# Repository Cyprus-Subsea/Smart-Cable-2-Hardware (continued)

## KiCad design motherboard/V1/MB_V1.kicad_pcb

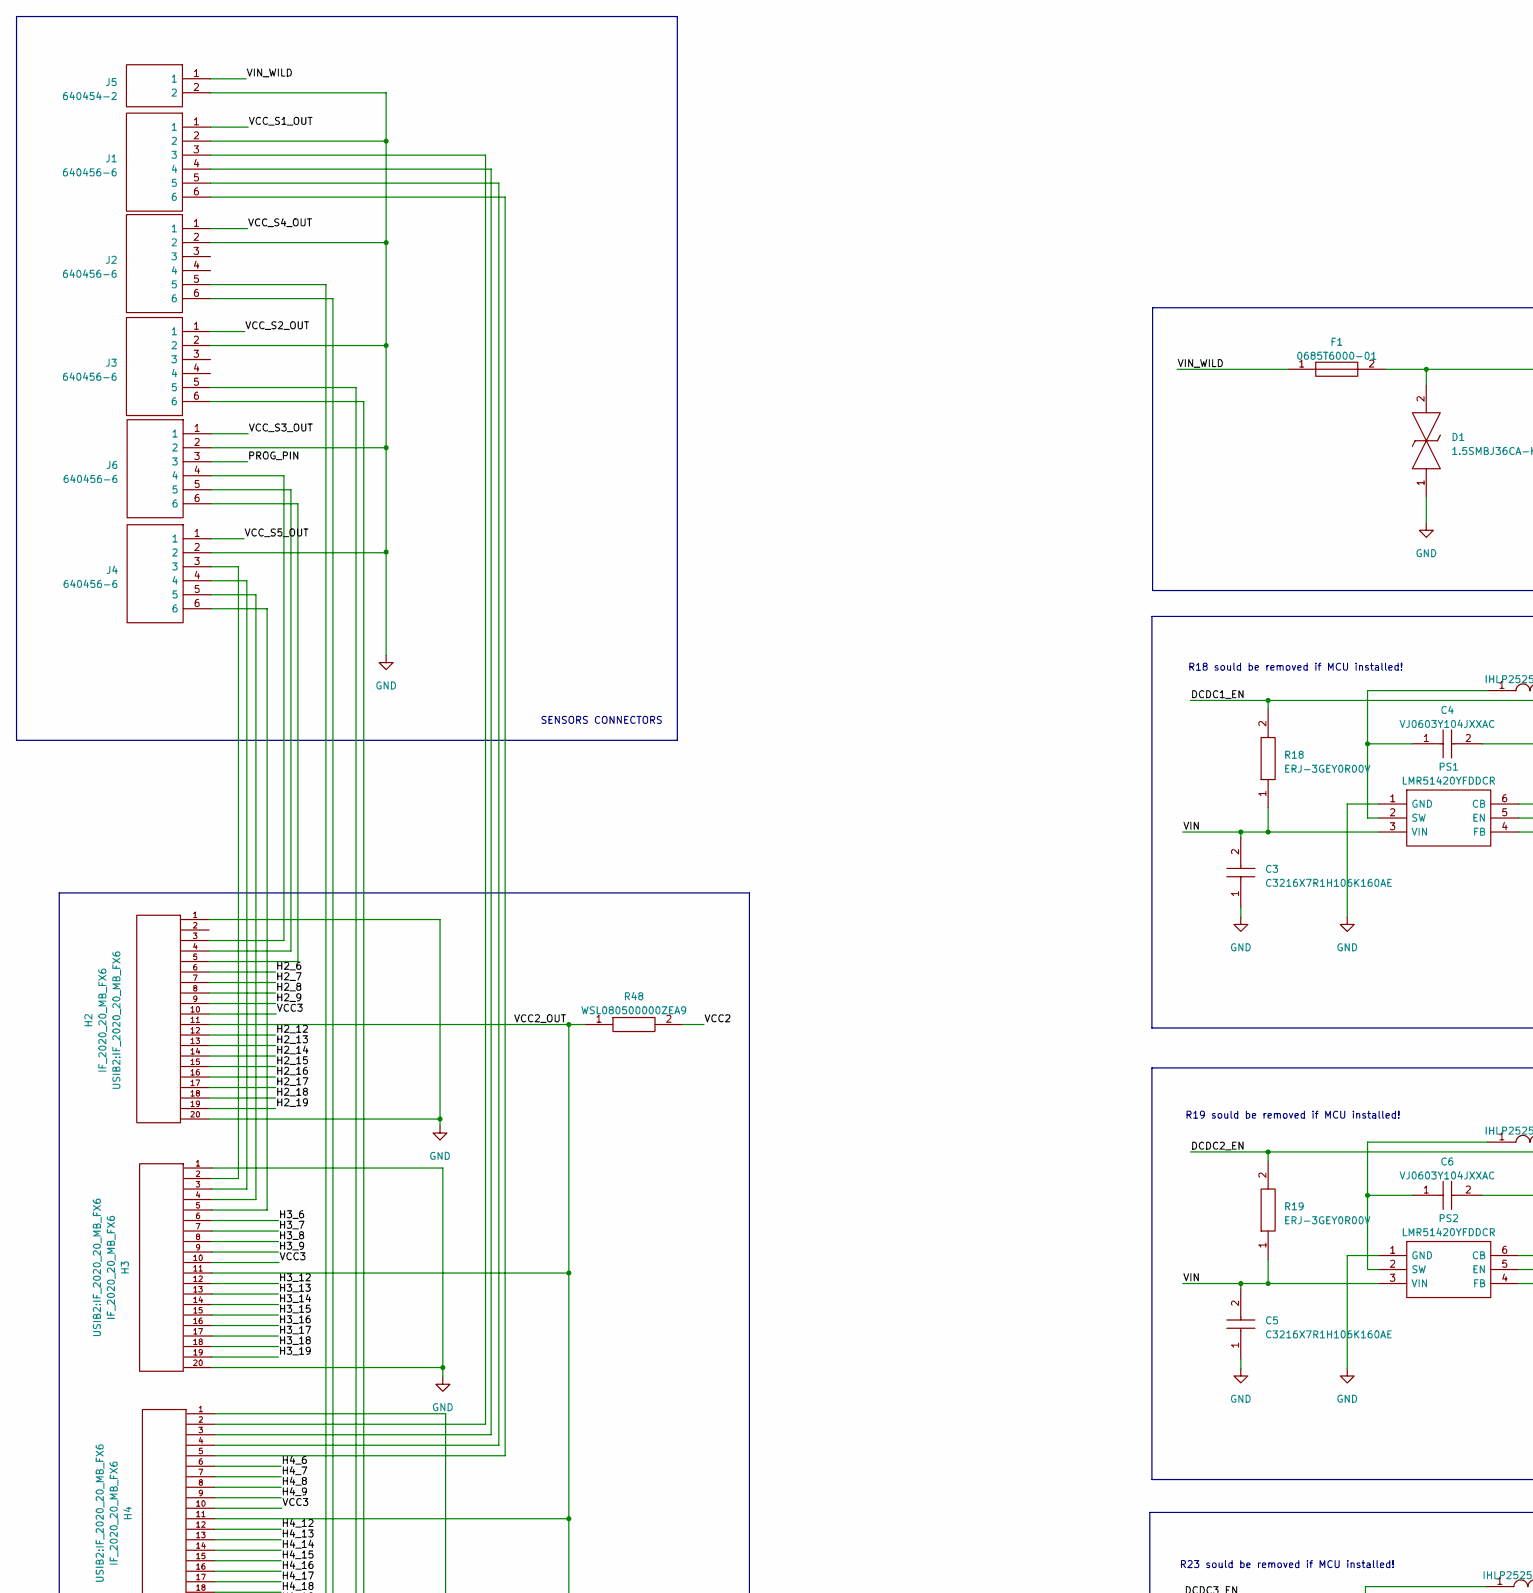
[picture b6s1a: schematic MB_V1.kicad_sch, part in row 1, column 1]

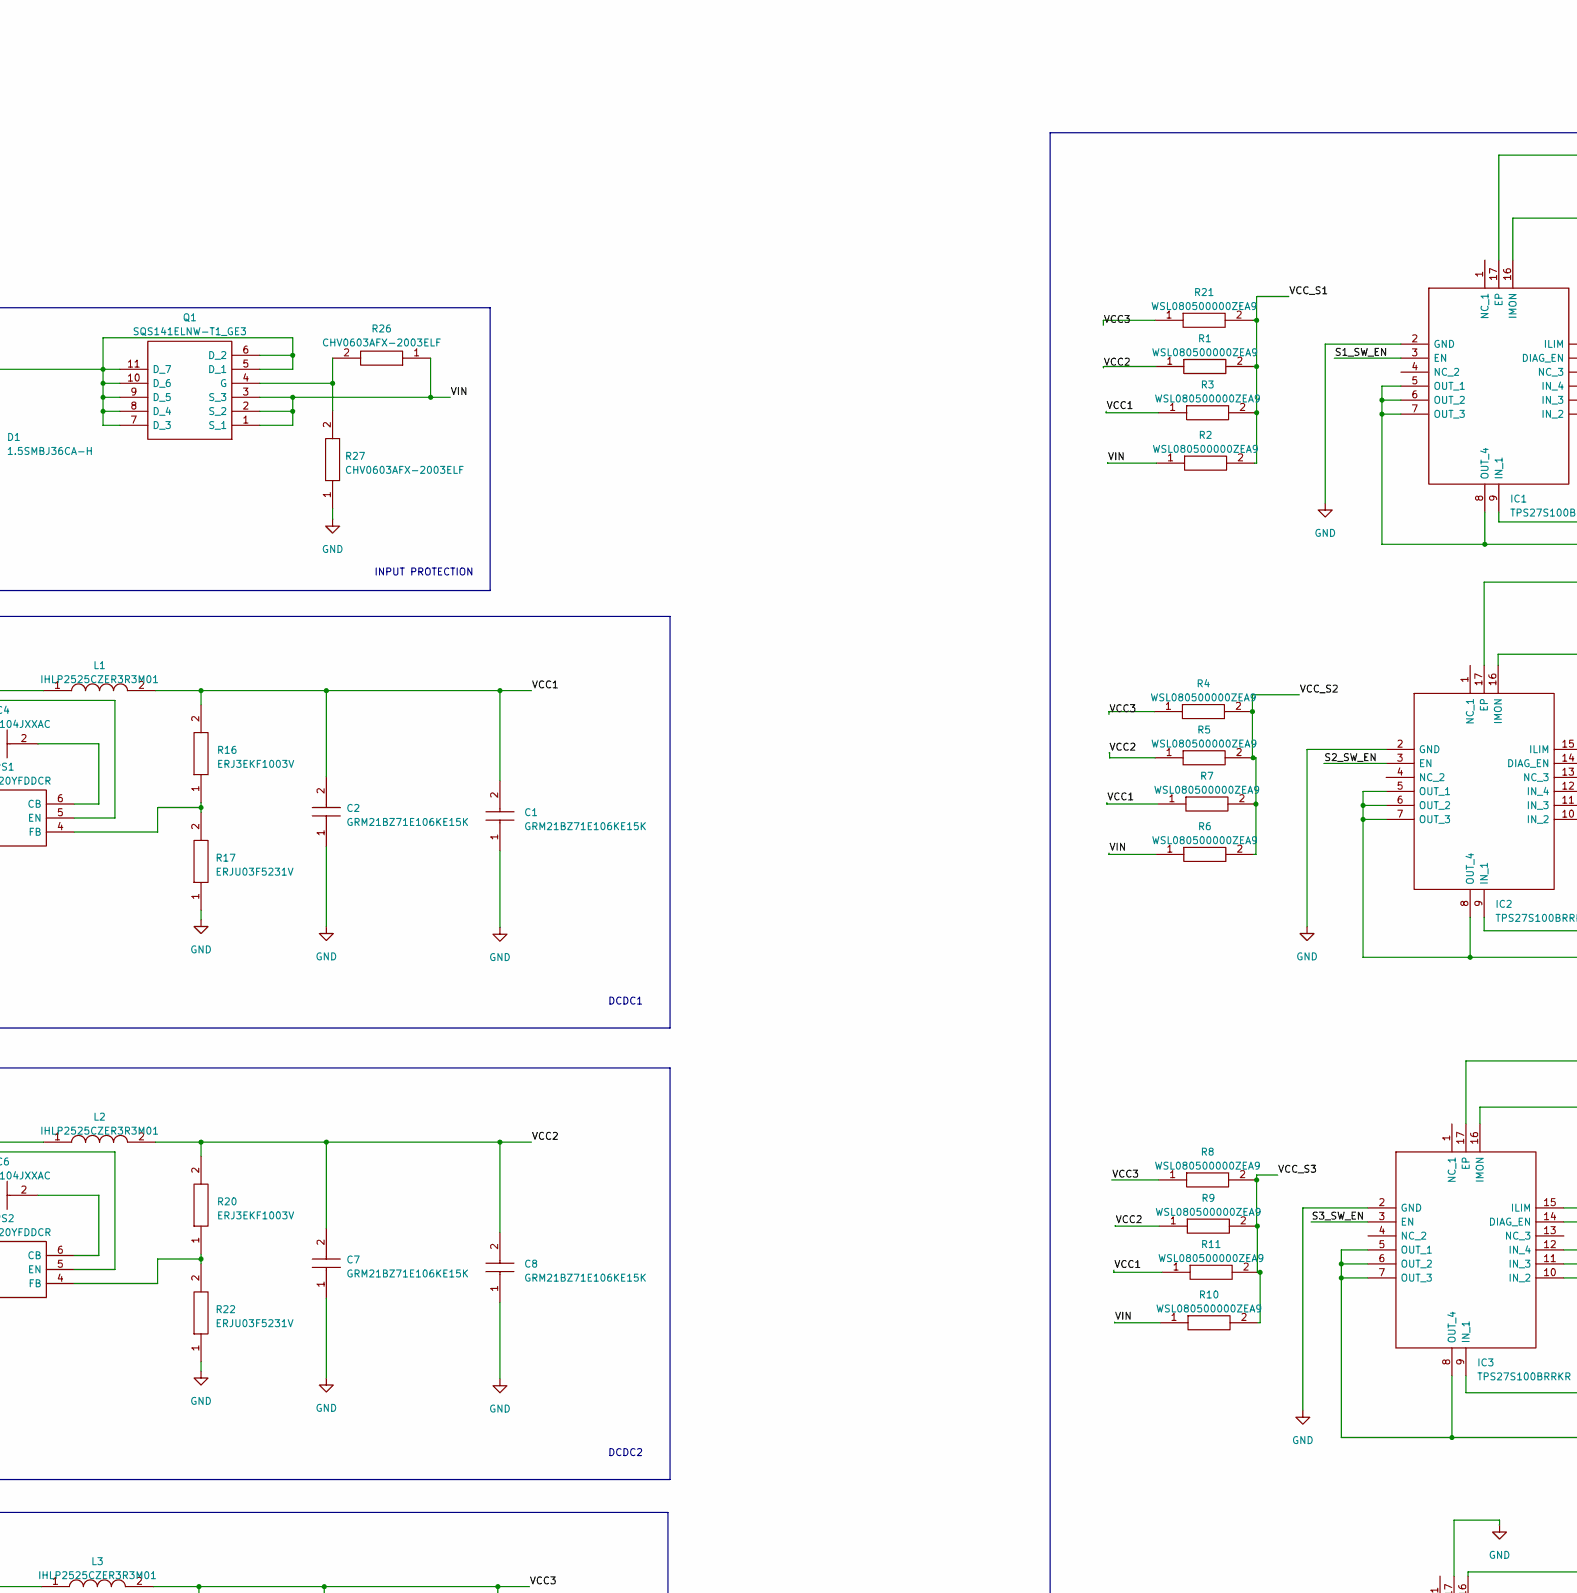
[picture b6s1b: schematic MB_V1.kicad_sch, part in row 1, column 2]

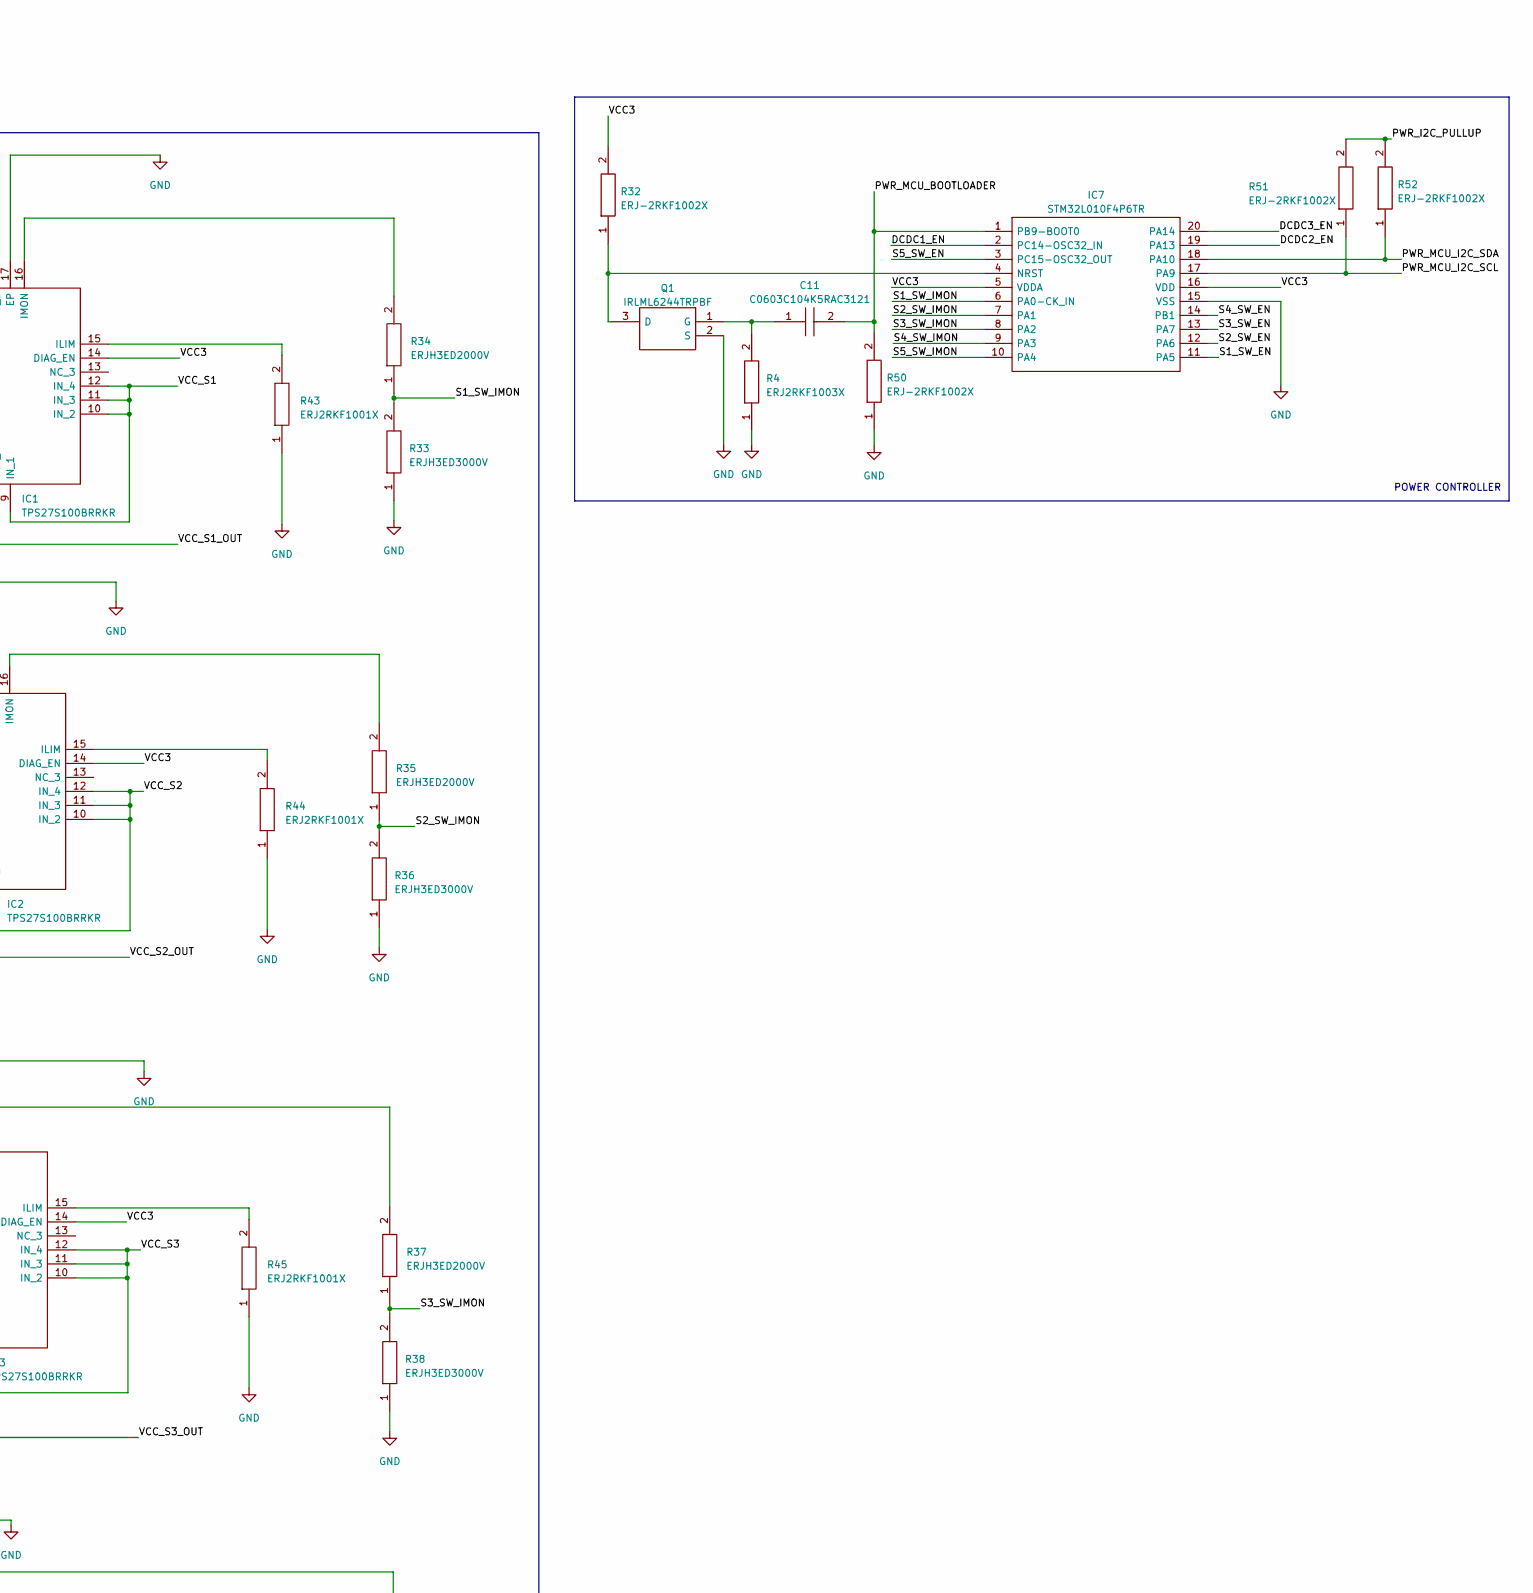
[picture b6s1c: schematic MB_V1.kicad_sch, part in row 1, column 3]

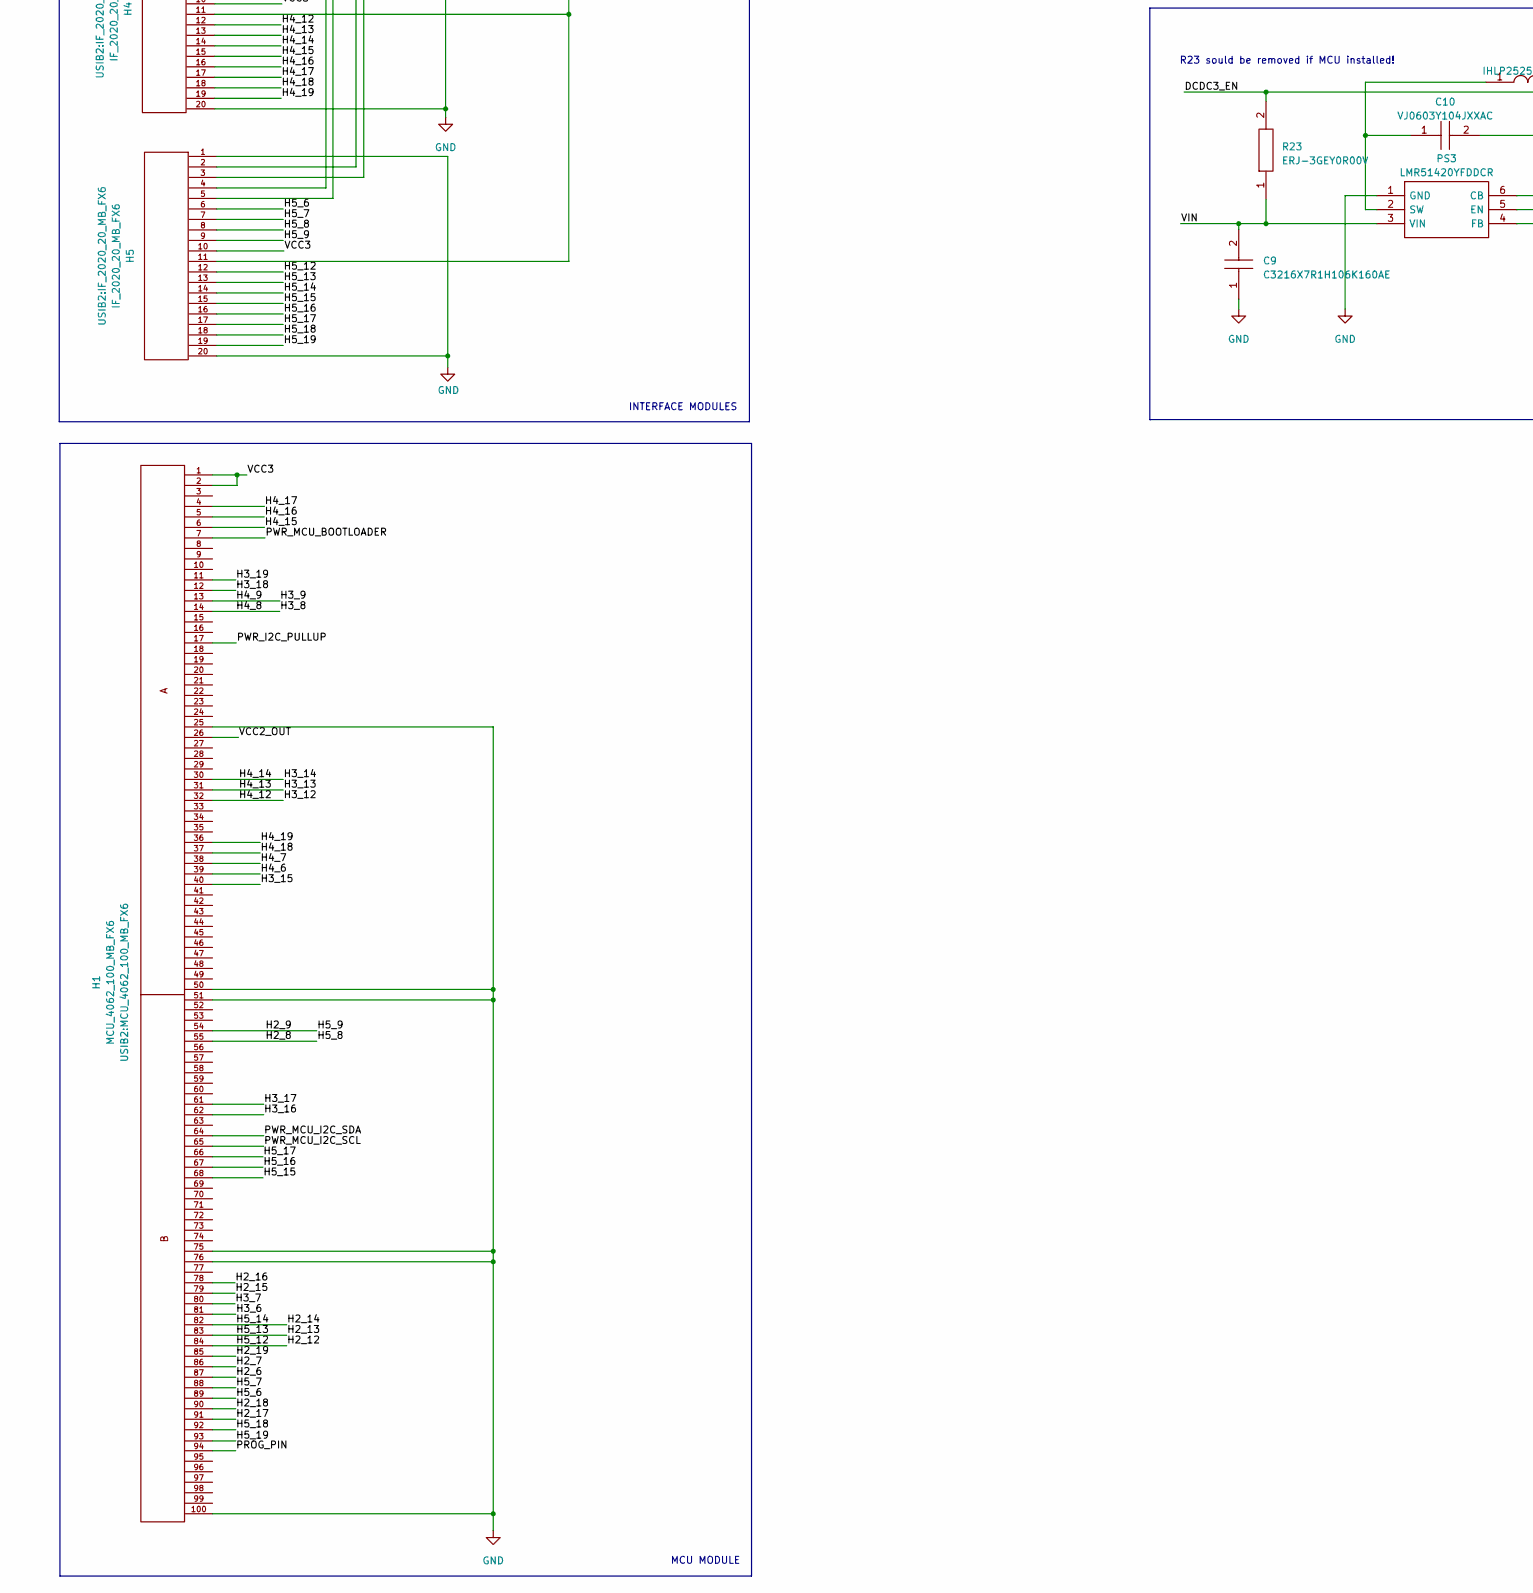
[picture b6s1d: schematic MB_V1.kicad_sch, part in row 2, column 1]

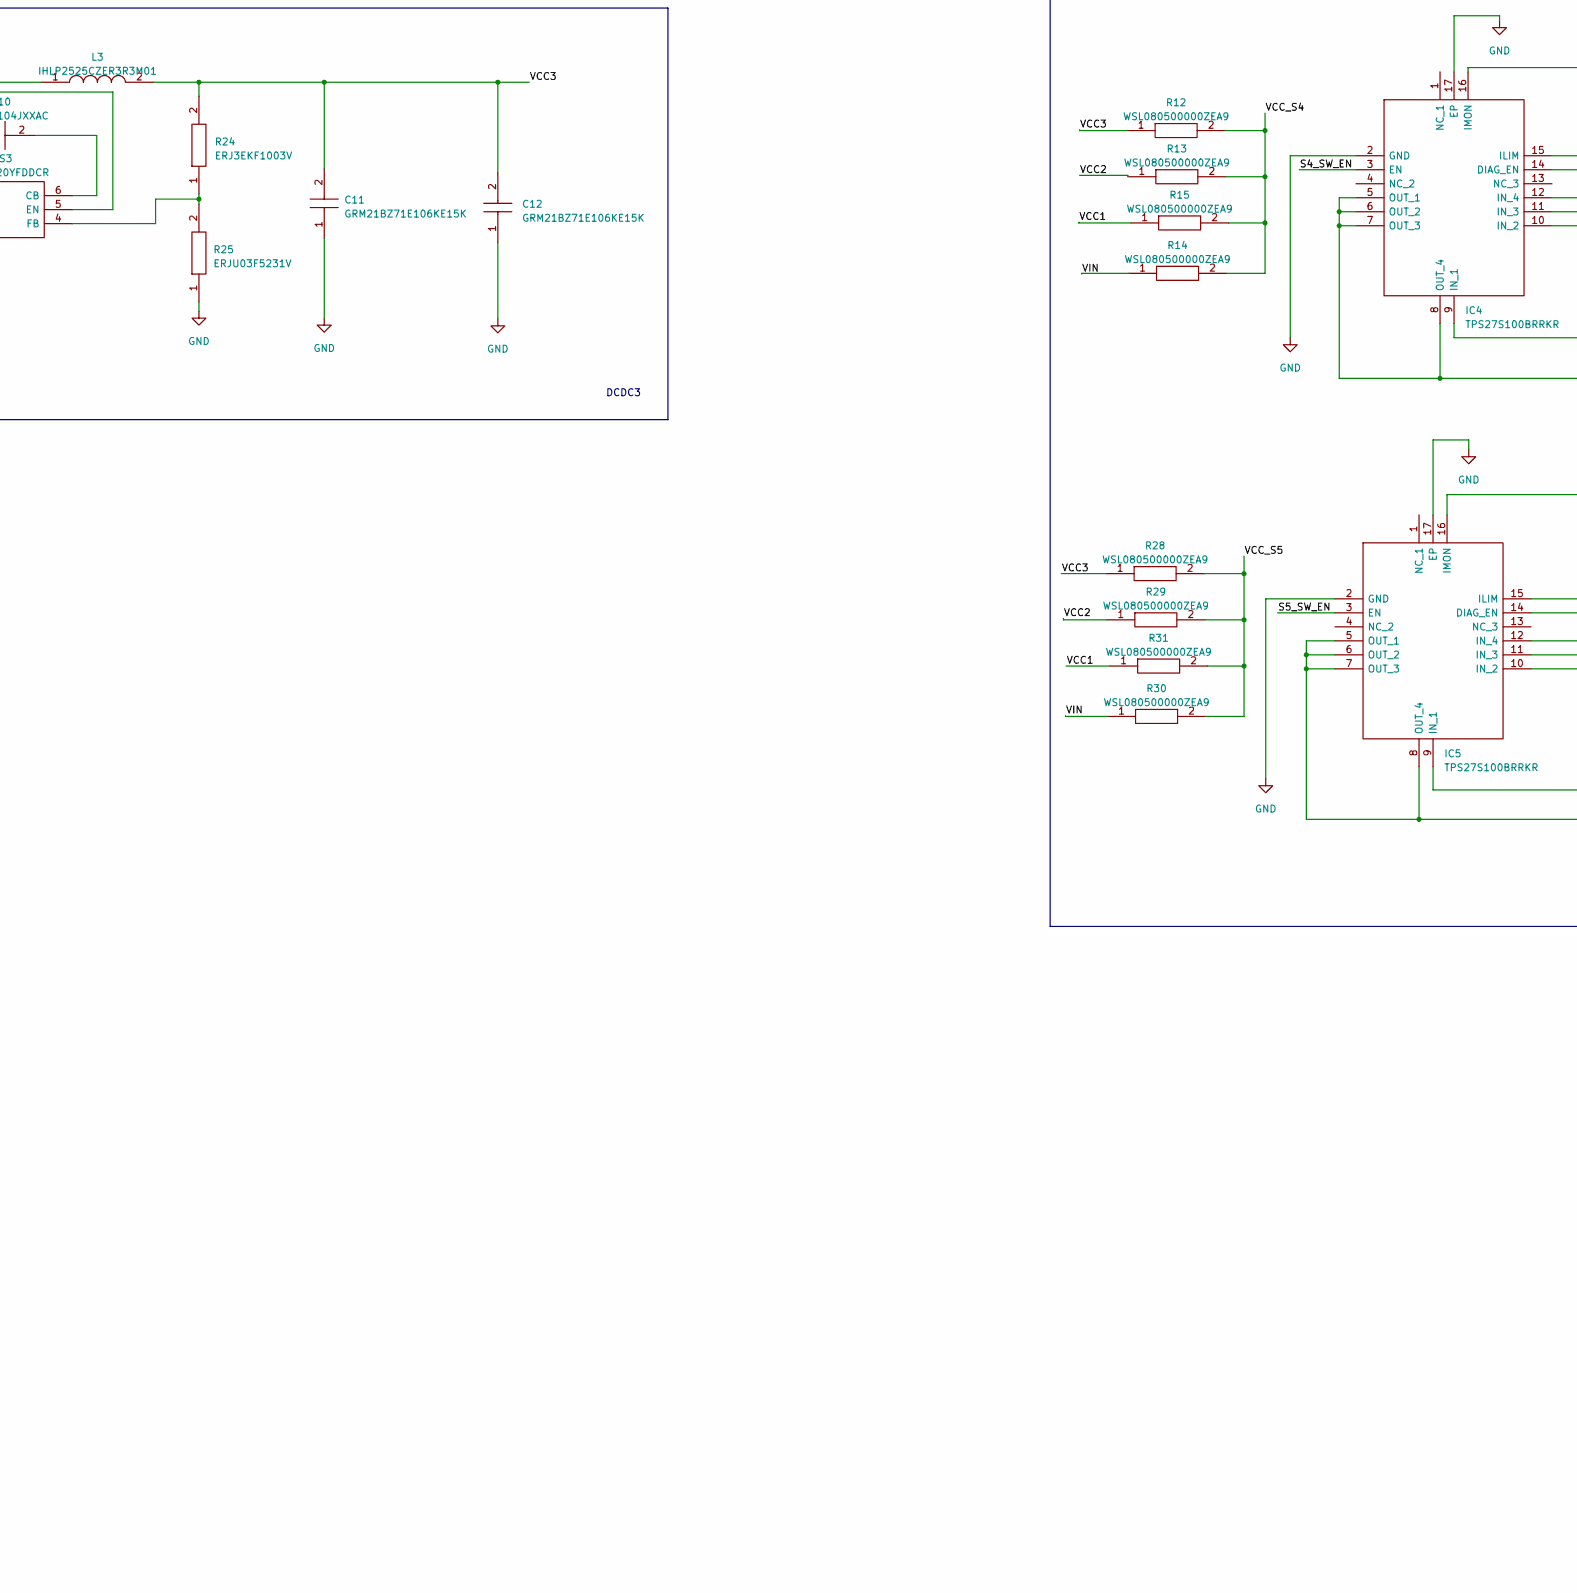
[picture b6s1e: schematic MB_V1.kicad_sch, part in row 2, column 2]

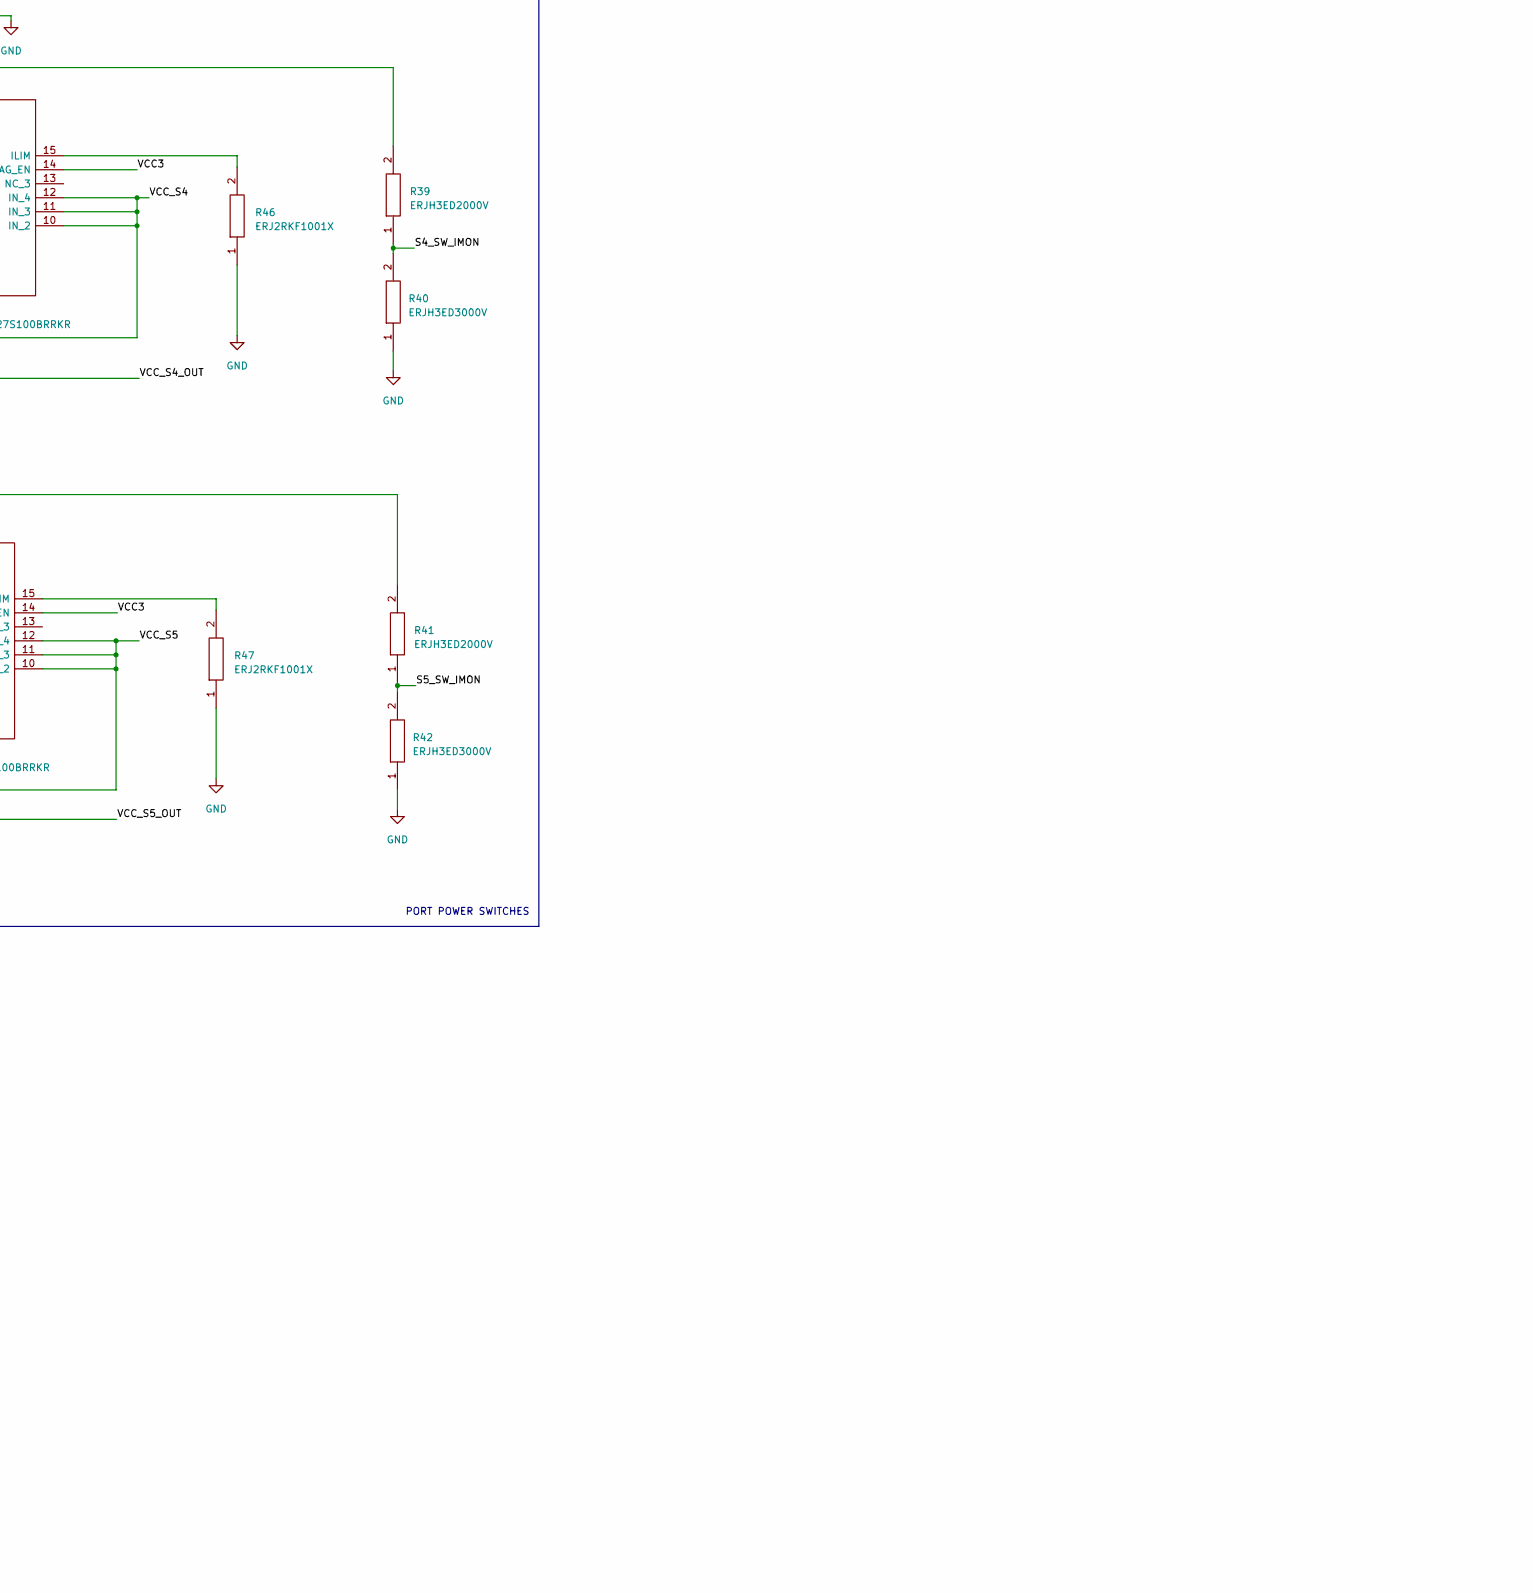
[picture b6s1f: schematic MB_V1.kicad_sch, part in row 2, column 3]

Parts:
C1, C2, C7, C8, C11, C12: GRM21BZ71E106KE15K; CAPC2012X145N; Manufacturer_Part_Number GRM21BZ71E106KE15K; Mouser Part Number 81-GRM21BZ71E106KE5K
C3, C5, C9: C3216X7R1H106K160AE; CAPC3216X180N; Manufacturer_Part_Number C3216X7R1H106K160AE; Mouser Part Number 810-C3216X7R1H106160
C4, C6, C10: VJ0603Y104JXXAC; CAPC1608X97N; Manufacturer_Part_Number VJ0603Y104JXXAC; Mouser Part Number 77-VJ0603Y104JXXAC
D1: 1.5SMBJ36CA-H; DIONM5436X244N; Manufacturer_Part_Number 1.5SMBJ36CA-H; Mouser Part Number 652-1.5SMBJ36CA-H
F1: 0685T6000-01; FUSC3216X83N; Manufacturer_Part_Number 0685T6000-01; Mouser Part Number 530-0685T6000-01
H1: MCU_4062_100_MB_FX6
H2, H3, H4, H5: IF_2020_20_MB_FX6
IC1, IC2, IC3, IC4, IC5: TPS27S100BRRKR; Manufacturer_Part_Number TPS27S100BRRKR; Mouser Part Number 595-TPS27S100BRRKR
IC7: STM32L010F4P6TR; SOP65P640X120-20N; Manufacturer_Part_Number STM32L010F4P6TR; Mouser Part Number 511-STM32L010F4P6TR
J1, J2, J3, J4, J6: 640456-6; SHDR6W66P0X254_1X6_1524X572X1003P; Manufacturer_Part_Number 640456-6; Mouser Part Number 571-6404566
J5: 640454-2; HDRV2W66P0X254_1X2_762X572X1003P; Manufacturer_Part_Number 640454-2; Mouser Part Number 571-640454-2
L1, L2, L3: IHLP2525CZER3R3M01; INDPM6965X300N; Manufacturer_Part_Number IHLP2525CZER3R3M01; Mouser Part Number 70-IHLP2525CZER3R3M0
PS1, PS2, PS3: LMR51420YFDDCR; SOT95P280X110-6N; Manufacturer_Part_Number LMR51420YFDDCR; Mouser Part Number 595-LMR51420YFDDCR
Q1: IRLML6244TRPBF; SOT95P237X112-3N; Manufacturer_Part_Number IRLML6244TRPBF; Mouser Part Number 942-IRLML6244TRPBF
R1, R2, R3, R4, R5, R6, R7, R8, R9, R10, R11, R12, R13, R14, R15, R21, R28, R29, R30, R31, R48: WSL080500000ZEA9; RESC2013X84N; Manufacturer_Part_Number WSL080500000ZEA9; Mouser Part Number 71-WSL080500000ZEA9
R16, R20, R24: ERJ3EKF1003V; ERJ3EKF1000V; Manufacturer_Part_Number ERJ3EKF1003V
R17, R22, R25: ERJU03F5231V; ERJS03J155V; Manufacturer_Part_Number ERJU03F5231V
R18, R19, R23: ERJ-3GEY0R00V; ERJ3EKF1000V; Manufacturer_Part_Number ERJ-3GEY0R00V; Mouser Part Number 667-ERJ-3GEY0R00V
R26, R27: CHV0603AFX-2003ELF; RESC1608X55N; Manufacturer_Part_Number CHV0603AFX-2003ELF; Mouser Part Number 652-CHV0603AFX2003LF
R32, R50, R51, R52: ERJ-2RKF1002X; ERJ2RKD1004X; Manufacturer_Part_Number ERJ-2RKF1002X; Mouser Part Number 667-ERJ-2RKF1002X
R33, R36, R38, R40, R42: ERJH3ED3000V; ERJH3; Manufacturer_Part_Number ERJH3ED3000V
R34, R35, R37, R39, R41: ERJH3ED2000V; ERJH3; Manufacturer_Part_Number ERJH3ED2000V
R43, R44, R45, R46, R47: ERJ2RKF1001X; ERJ2RKD1004X; Manufacturer_Part_Number ERJ2RKF1001X

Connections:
/DCDC1_EN: IC7.2 (PC14-OSC32_IN), PS1.5 (EN), R18.2
/DCDC2_EN: IC7.19 (PA13), PS2.5 (EN), R19.2
/DCDC3_EN: IC7.20 (PA14), PS3.5 (EN), R23.2
/H2_6: H1.87, H2.6
/H2_7: H1.86, H2.7
/H2_8: H1.55, H2.8, H5.8
/H2_9: H1.54, H2.9, H5.9
/H2_12: H1.84, H2.12, H5.12
/H2_13: H1.83, H2.13, H5.13
/H2_14: H1.82, H2.14, H5.14
/H2_15: H1.79, H2.15
/H2_16: H1.78, H2.16
/H2_17: H1.91, H2.17
/H2_18: H1.90, H2.18
/H2_19: H1.85, H2.19
/H3_6: H1.81, H3.6
/H3_7: H1.80, H3.7
/H3_8: H1.14, H3.8, H4.8
/H3_9: H1.13, H3.9, H4.9
/H3_12: H1.32, H3.12, H4.12
/H3_13: H1.31, H3.13, H4.13
/H3_14: H1.30, H3.14, H4.14
/H3_15: H1.40, H3.15
/H3_16: H1.62, H3.16
/H3_17: H1.61, H3.17
/H3_18: H1.12, H3.18
/H3_19: H1.11, H3.19
/H4_6: H1.39, H4.6
/H4_7: H1.38, H4.7
/H4_15: H1.6, H4.15
/H4_16: H1.5, H4.16
/H4_17: H1.4, H4.17
/H4_18: H1.37, H4.18
/H4_19: H1.36, H4.19
/H5_6: H1.89, H5.6
/H5_7: H1.88, H5.7
/H5_15: H1.68, H5.15
/H5_16: H1.67, H5.16
/H5_17: H1.66, H5.17
/H5_18: H1.92, H5.18
/H5_19: H1.93, H5.19
/PROG_PIN: H1.94, J6.3
/PWR_I2C_PULLUP: H1.17, R51.2, R52.2
/PWR_MCU_I2C_SCL: H1.65, IC7.17 (PA9), R51.1
/PWR_MCU_I2C_SDA: H1.64, IC7.18 (PA10), R52.1
/S1_SW_EN: IC1.3 (EN), IC7.11 (PA5); also elsewhere on the board
/S1_SW_IMON: IC7.6 (PA0-CK_IN), R33.2, R34.1
/S2_SW_EN: IC2.3 (EN), IC7.12 (PA6); also elsewhere on the board
/S2_SW_IMON: IC7.7 (PA1), R35.1, R36.2
/S3_SW_EN: IC3.3 (EN), IC7.13 (PA7); also elsewhere on the board
/S3_SW_IMON: IC7.8 (PA2), R37.1, R38.2
/S4_SW_EN: IC4.3 (EN), IC7.14 (PB1); also elsewhere on the board
/S4_SW_IMON: IC7.9 (PA3), R39.1, R40.2
/S5_SW_EN: IC5.3 (EN), IC7.3 (PC15-OSC32_OUT); also elsewhere on the board
/S5_SW_IMON: IC7.10 (PA4), R41.1, R42.2
/VCC1: C1.2, C2.2, L1.2, R3.1, R7.1, R11.1, R15.1, R16.2, R31.1
/VCC2: C7.2, C8.2, L2.2, R1.1, R5.1, R9.1, R13.1, R20.2, R29.1, R48.2
/VCC2_OUT: H1.26, H2.11, H3.11, H4.11, H5.11, R48.1
/VCC_S1: IC1.9 (IN_1), IC1.10 (IN_2), IC1.11 (IN_3), IC1.12 (IN_4), R1.2, R2.2, R3.2, R21.2
/VCC_S1_OUT: IC1.5 (OUT_1), IC1.6 (OUT_2), IC1.7 (OUT_3), IC1.8 (OUT_4), J1.1
/VCC_S2_OUT: IC2.5 (OUT_1), IC2.6 (OUT_2), IC2.7 (OUT_3), IC2.8 (OUT_4), J3.1
/VCC_S3: IC3.9 (IN_1), IC3.10 (IN_2), IC3.11 (IN_3), IC3.12 (IN_4), R8.2, R9.2, R10.2, R11.2
/VCC_S3_OUT: IC3.5 (OUT_1), IC3.6 (OUT_2), IC3.7 (OUT_3), IC3.8 (OUT_4), J6.1
/VCC_S4: IC4.9 (IN_1), IC4.10 (IN_2), IC4.11 (IN_3), IC4.12 (IN_4), R12.2, R13.2, R14.2, R15.2
/VCC_S4_OUT: IC4.5 (OUT_1), IC4.6 (OUT_2), IC4.7 (OUT_3), IC4.8 (OUT_4), J2.1
/VCC_S5: IC5.9 (IN_1), IC5.10 (IN_2), IC5.11 (IN_3), IC5.12 (IN_4), R28.2, R29.2, R30.2, R31.2
/VCC_S5_OUT: IC5.5 (OUT_1), IC5.6 (OUT_2), IC5.7 (OUT_3), IC5.8 (OUT_4), J4.1
/VIN_WILD: F1.1, J5.1
unnamed: H2.3, J6.4
unnamed: H2.4, J6.5
unnamed: H2.5, J6.6
unnamed: H3.2, J4.3
unnamed: H3.3, J4.4
unnamed: H3.4, J4.5
unnamed: H3.5, J4.6
unnamed: H4.2, J1.3
unnamed: H4.3, J1.4
unnamed: H4.4, J1.5
unnamed: H4.5, J1.6
unnamed: H5.2, J3.5
unnamed: H5.3, J3.6
unnamed: H5.4, J2.5
unnamed: H5.5, J2.6
unnamed: IC1.15 (ILIM), R43.2
unnamed: IC1.16 (IMON), R34.2
unnamed: IC2.15 (ILIM), R44.2
unnamed: IC2.16 (IMON), R35.2
unnamed: IC3.15 (ILIM), R45.2
unnamed: IC3.16 (IMON), R37.2
unnamed: IC4.15 (ILIM), R46.2
unnamed: IC4.16 (IMON), R39.2
unnamed: IC5.15 (ILIM), R47.2
unnamed: IC5.16 (IMON), R41.2
unnamed: C4.2, PS1.6 (CB)
unnamed: PS1.4 (FB), R16.1, R17.2
unnamed: C4.1, L1.1, PS1.2 (SW)
unnamed: C6.2, PS2.6 (CB)
unnamed: PS2.4 (FB), R20.1, R22.2
unnamed: C6.1, L2.1, PS2.2 (SW)
unnamed: C10.2, PS3.6 (CB)
unnamed: PS3.4 (FB), R24.1, R25.2
unnamed: C10.1, L3.1, PS3.2 (SW)
unnamed: D1.2, F1.2, Q1.5 (D_1), Q1.6 (D_2), Q1.7 (D_3), Q1.8 (D_4), Q1.9 (D_5), Q1.10 (D_6), Q1.11 (D_7)
unnamed: Q1.4 (G), R26.2, R27.2

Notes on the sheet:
INTERFACE MODULES
DCDC2
DCDC3
R18 sould be removed if MCU installed!
MCU MODULE
POWER CONTROLLER
SENSORS CONNECTORS
R23 sould be removed if MCU installed!
DCDC1
PORT POWER SWITCHES
R19 sould be removed if MCU installed!
INPUT PROTECTION

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
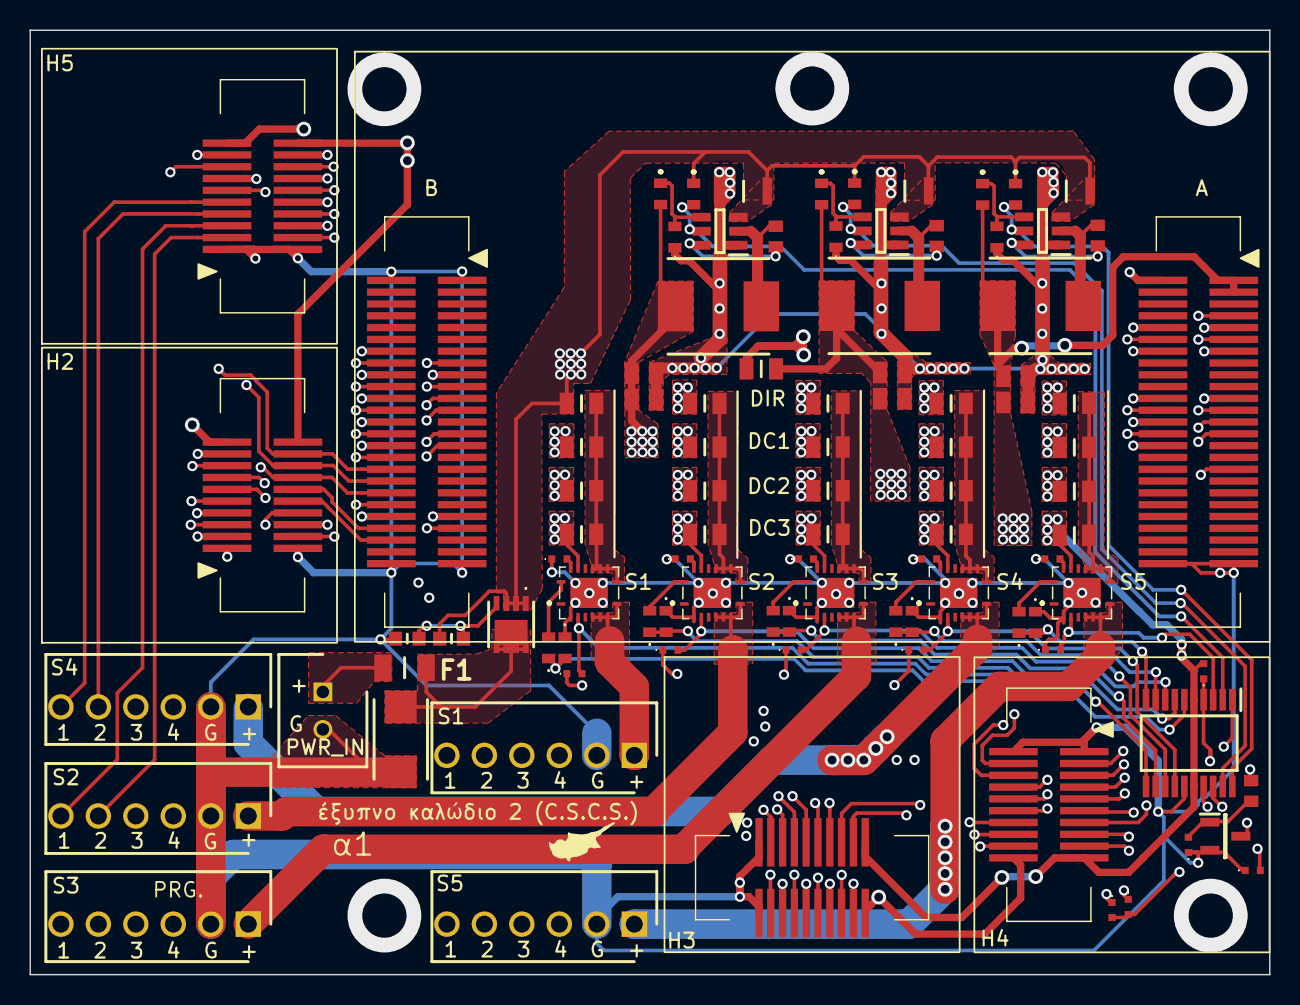
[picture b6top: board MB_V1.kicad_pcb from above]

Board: 4 copper layers, 84.0 x 64.0 mm, 97 parts (0 on the bottom side), 111 nets.

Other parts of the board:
C13: C0603C104K5RAC3121; CAPC1608X95N
Q2: IRLML6244TRPBF; SOT95P237X112-3N
R49: ERJ2RKF1003X; ERJ2RKD1004X
R53, R54, R55, R56, R57: ERJ-2RKF1002X; ERJ2RKD1004X

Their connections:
/S1_SW_EN: R53.2; also elsewhere on the board
/S2_SW_EN: R54.2; also elsewhere on the board
/S3_SW_EN: R55.2; also elsewhere on the board
/S4_SW_EN: R56.2; also elsewhere on the board
/S5_SW_EN: R57.2; also elsewhere on the board
unnamed: C13.1, Q2.1 (G), R49.2

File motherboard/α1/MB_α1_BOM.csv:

Ref,Qnty,Value,Cmp name,Footprint,Description,Vendor
"C1, C2, C7, C8, C11, C12, ",6,GRM21BZ71E106KE15K,GRM21BZ71E106KE15K,CAPC2012X145N,Multilayer Ceramic Capacitors MLCC - SMD/SMT,
"C3, C5, C9, ",3,C3216X7R1H106K160AE,C3216X7R1H106K160AE,CAPC3216X180N,"MULTILAYER CERAMIC CHIP CAPACITORS, 3216, Commercial grade, general (Up to 75V)",
"C4, C6, C10, ",3,VJ0603Y104JXXAC,VJ0603Y104JXXAC,CAPC1608X97N,Multilayer Ceramic Capacitors MLCC - SMD/SMT .1UF 25V 5% 0603,
"C13, ",1,C0603C104K5RAC3121,C0603C104K5RAC3121,CAPC1608X95N,Multilayer Ceramic Capacitors MLCC - SMD/SMT 50V .1uF X7R 0603 10% AEC-Q200,
"D1, ",1,1.5SMBJ36CA-H,1.5SMBJ36CA-H,DIONM5436X244N,"DIO TVS VRWM 36V 1500W BIDIR SMB 7"" REEL",
"F1, ",1,0685T6000-01,0685T6000-01,FUSC3216X83N,"Surface Mount Fuses Surface Mt Slow Blow 1206 size, 6A",
"IC1, IC2, IC3, IC4, IC5, ",5,TPS27S100BRRKR,TPS27S100BRRKR,TPS27S100BRRKR,"Power Switch ICs - Power Distribution 40-V, 4-A, 80-m Single-Channel High-Side Switch",
"IC7, ",1,STM32L010F4P6TR,STM32L010F4P6TR,SOP65P640X120-20N,MCU 32-bit ARM Cortex M0+ RISC 16KB Flash 2.5V/3.3V 20-Pin TSSOP T/R,
"J1, J2, J3, J4, J6, ",5,640456-6,640456-6,SHDR6W66P0X254_1X6_1524X572X1003P,Headers & Wire Housings FRICTION LCK HDR 6P Straight Post tin,
"J5, ",1,640454-2,640454-2,HDRV2W66P0X254_1X2_762X572X1003P,"2 way MTA straight polarised header TE Connectivity MTA-100 Series, 2.54mm Pitch 2 Way 1 Row Straight PCB Header, Solder Termination, 5A",
"L1, L2, L3, ",3,IHLP2525CZER3R3M01,IHLP2525CZER3R3M01,INDPM6965X300N,"Vishay, IHLP, 2225 (5664M) Shielded Wire-wound SMD Inductor with a Metal Composite Core, 3.3 uH +/-20% Shielded 6A Idc",
"PS1, PS2, PS3, ",3,LMR51420YFDDCR,LMR51420YFDDCR,SOT95P280X110-6N,"Switching Voltage Regulators SIMPLE SWITCHER power converter 4.5-V to 36-V, 2-A, synchronous buck with 40-uA IQ",
"Q1, ",1,SQS141ELNW-T1_GE3,SQS141ELNW-T1_GE3,SQS850ENT1_GE3,Automotive P-Channel 40 V (D-S) 175 C MOSFET,
"Q2, ",1,IRLML6244TRPBF,IRLML6244TRPBF,SOT95P237X112-3N,"INFINEON - IRLML6244TRPBF - MOSFET, N CH, 20V, 6.3A, SOT-23",
"R1, R2, R3, R4, R5, R6, R7, R8, R9, R10, R11, R12, R13, R14, R15, R21, R28, R29, R30, R31, R48, ",21,WSL080500000ZEA9,WSL080500000ZEA9,RESC2013X84N,"VISHAY - WSL080500000ZEA9 - SMD Chip Resistor, Jumper, 0805 [2012 Metric], 0 ohm, WSL-9 Series, Metal Strip",
"R16, R20, R24, ",3,ERJ3EKF1003V,ERJ3EKF1003V,ERJ3EKF1000V,"PANASONIC ELECTRONIC COMPONENTS - ERJ3EKF1003V - RES, THICK FILM, 100K, 1%, 0.1W, 0603",
"R17, R22, R25, ",3,ERJU03F5231V,ERJU03F5231V,ERJS03J155V,"Anti-Sulfurated Thick Film Chip Resistor, 0603, 0.1W",
"R18, R19, R23, ",3,ERJ-3GEY0R00V,ERJ-3GEY0R00V,ERJ3EKF1000V,Thick Film Resistors - SMD 0603 Zero Ohms,
"R26, R27, ",2,CHV0603AFX-2003ELF,CHV0603AFX-2003ELF,RESC1608X55N,ResHV A 0603 200k 1% 0.1W TCR100,
"R32, R50, R51, R52, R53, R54, R55, R56, R57, ",9,ERJ-2RKF1002X,ERJ-2RKF1002X,ERJ2RKD1004X,Res Thick Film 0402 10K Ohm 1% 0.1W(1/10W) +/-100ppm/C Pad SMD Automotive T/R,
"R33, R36, R38, R40, R42, ",5,ERJH3ED3000V,ERJH3ED3000V,ERJH3,"Power Rating 0.125W,Resistance 300 Ohm,LxW(EIA) 1.6 x 0.8 (EIA:0603) mm",
"R34, R35, R37, R39, R41, ",5,ERJH3ED2000V,ERJH3ED2000V,ERJH3,"Power Rating 0.125W,Resistance 200 Ohm,LxW(EIA) 1.6 x 0.8 (EIA:0603) mm",
"R43, R44, R45, R46, R47, ",5,ERJ2RKF1001X,ERJ2RKF1001X,ERJ2RKD1004X,"Precision,Thick,Chip Resistors,Size1005 Panasonic Precision Thick Film Surface Mount Resistor 0402 Case 1k +/-1% 0.1W +/-100ppm/C",
"R49, ",1,ERJ2RKF1003X,ERJ2RKF1003X,ERJ2RKD1004X,Panasonic ERJ2RK Series Thick Film Surface Mount Fixed Resistor 0402 Case +/-1% 0.1W +/-100ppm/C,

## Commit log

2022-11-21 init commit
2023-05-30 MB_V1 MCU_V1
2023-05-30 MB_V1 changed
2023-06-05 MB V1 finished
2023-06-06 MB V1 finished again
2023-06-06 Versions names changed to greek
2023-06-06 RS232-2 updated
2023-06-07 IMU added
2023-06-07 DIRECT I2C added
2023-06-07 MCU α2 added
